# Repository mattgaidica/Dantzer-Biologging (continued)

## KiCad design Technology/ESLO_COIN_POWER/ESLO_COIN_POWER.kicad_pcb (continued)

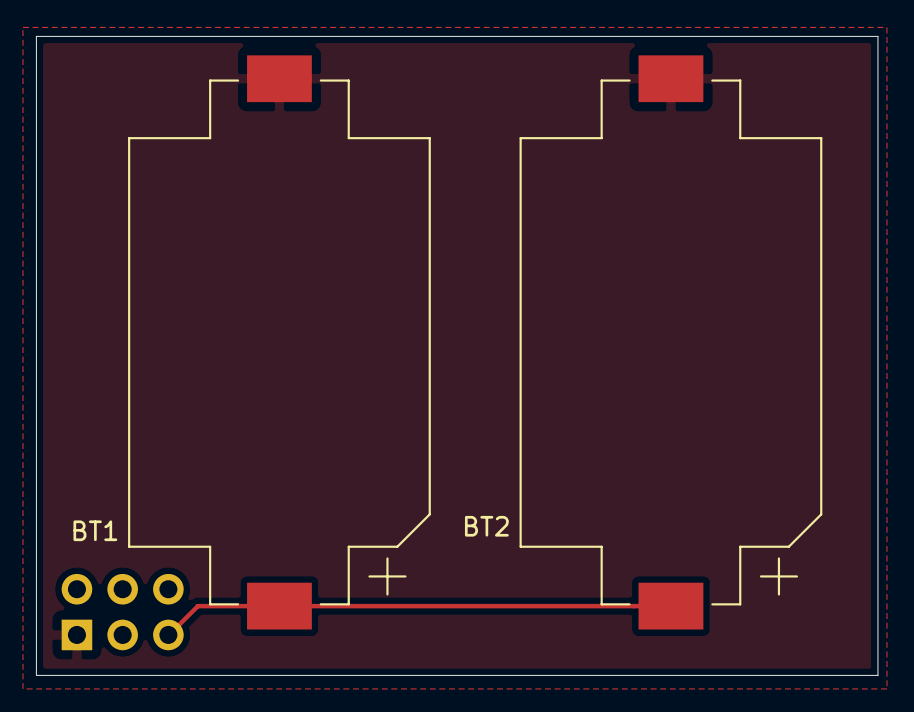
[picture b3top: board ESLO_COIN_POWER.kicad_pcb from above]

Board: 2 copper layers, 46.8 x 35.5 mm, 3 parts (1 on the bottom side), 2 nets.

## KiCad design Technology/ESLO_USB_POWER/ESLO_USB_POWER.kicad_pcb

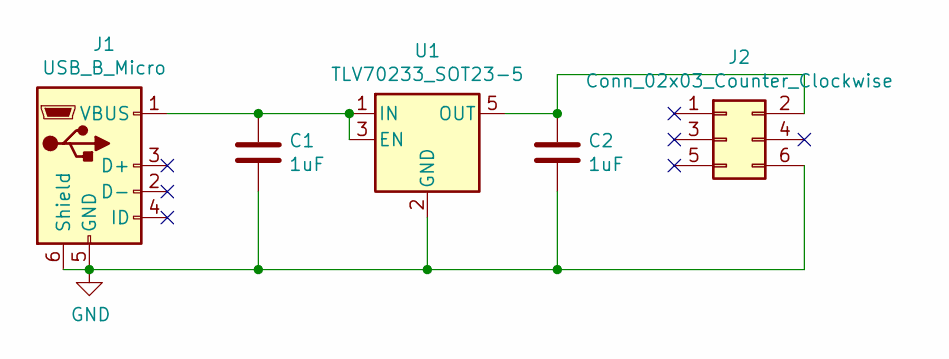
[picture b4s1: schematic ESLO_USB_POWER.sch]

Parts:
C1, C2: 1uF; C_0603_1608Metric; Digikey 399-11133-2-ND
J1: USB_B_Micro; USB_Micro-B_Molex-105017-0001; Digikey WM11262TR-ND
J2: Conn_02x03_Counter_Clockwise; PinSocket_2x03_P2.54mm_Vertical; Digikey A106656-ND
U1: TLV70233_SOT23-5; SOT-23-5; Digikey 296-39284-2-ND

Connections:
GND: C1.2, C2.2, J1.5 (GND), J1.6 (Shield), J2.6, U1.2 (GND)
unnamed: C1.1, J1.1 (VBUS), U1.1 (IN), U1.3 (EN)
unnamed: C2.1, J2.2, U1.5 (OUT)

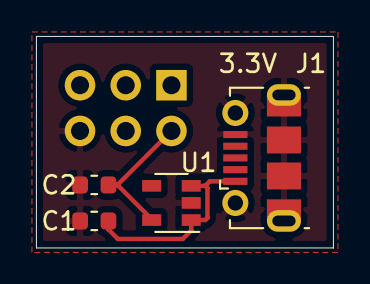
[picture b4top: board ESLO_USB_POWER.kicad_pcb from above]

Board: 2 copper layers, 16.5 x 11.8 mm, 5 parts (1 on the bottom side), 3 nets.

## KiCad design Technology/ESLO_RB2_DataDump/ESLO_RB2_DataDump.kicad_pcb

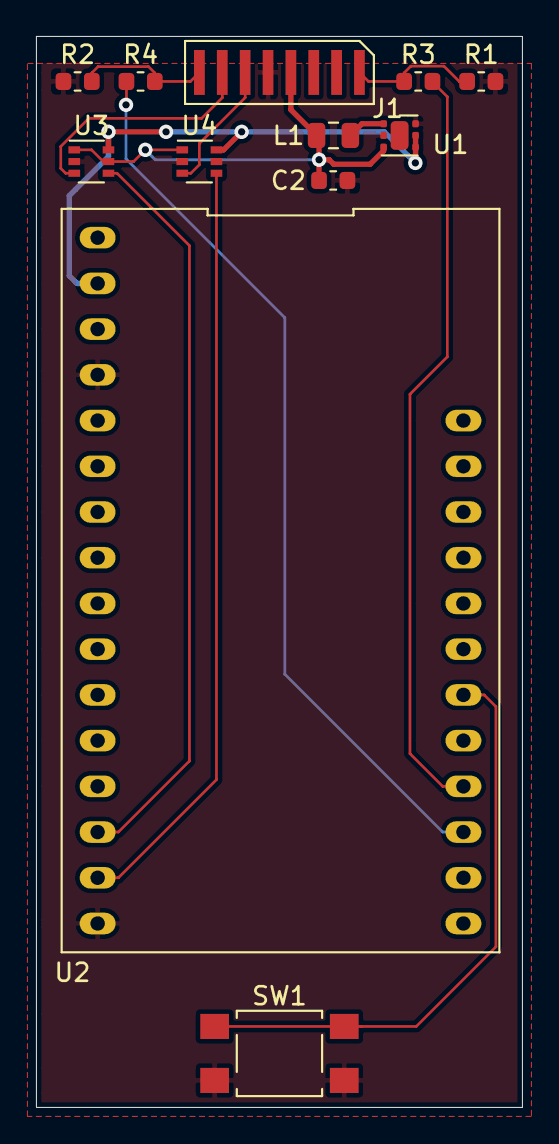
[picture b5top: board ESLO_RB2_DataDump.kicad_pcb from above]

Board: 2 copper layers, 27.0 x 59.5 mm, 12 parts (0 on the bottom side), 13 nets.

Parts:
C2: 10uF; C_0603_1608Metric
J1: Conn_01x08_Female; 8pin_1-27pitch_SMD
L1: 2.2uH; L_0805_2012Metric
R1, R2: 10k; R_0603_1608Metric
R3, R4: 8.25k; R_0603_1608Metric
SW1: SW_DPST; SW_SPST_TL3305A
U1: TPS62243_WSON; WSON-6-1EP_2x2mm_P0.65mm_EP1x1.6mm
U2: Adalogger; Adafruit_feather
U3, U4: SN74ACX1T45; SOT-363_SC-70-6

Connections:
+1V8: C2.1, J1.4, L1.2, U1.3, U3.1, U3.5, U4.1
+3V3: U1.4, U1.5, U2.2, U3.6, U4.6
DEBUG: R4.1, U2.19
GND: C2.2, J1.5, R1.1, R2.1, SW1.2, U1.2, U1.6, U2.4, U2.16, U3.2, U4.2, U4.5
unnamed: J1.1, R1.2, R3.2
unnamed: J1.8, R2.2, R4.2
unnamed: L1.1, U1.1
unnamed: SW1.1, U2.22
RESET: R3.1, U2.20
RX: U2.14, U3.4
RXD: J1.6, U4.3
TX: U2.15, U4.4
TXD: J1.7, U3.3

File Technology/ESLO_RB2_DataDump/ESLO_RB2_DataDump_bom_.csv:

Component,Description,Part,References,Value,Footprint,Quantity Per PCB,Datasheet,Digikey
1,Unpolarized capacitor,C,C2,10uF,C_0603_1608Metric,1,~,478-8050-1-ND
2,"Generic connector, single row, 01x08, script generated (kicad-library-utils/schlib/autogen/connector/)",Conn_01x08_Female,J1,Conn_01x08_Female,8pin_1-27pitch_SMD,1,~,ED90570-ND
3,Capacitor symbol for simulation only,INDUCTOR,L1,2.2uH,L_0805_2012Metric,1,~,490-4994-1-ND
4,Resistor,R,R1 R2,10k,R_0603_1608Metric,2,~,CR0603-JW-103ELFCT-ND
5,Resistor,R,R3 R4,8.25k,R_0603_1608Metric,2,~,RMCF0603FT8K25CT-ND
6,Double Pole Single Throw (DPST) Switch,SW_DPST,SW1,SW_DPST,SW_SPST_TL3305A,1,~,EG5353CT-ND
7,,Adalogger,U2,Adalogger,Adafruit_feather,1,,1528-1539-ND
8,,SN74ACX1T45,U3 U4,SN74ACX1T45,SOT-363_SC-70-6,2,,296-SN74AXC1T45QDCKRQ1CT-ND
9,,TPS62243_WSON,U1,TPS62243_WSON,WSON-6-1EP_2x2mm_P0.65mm_EP1x1.6mm,1,,TPS62243DRVR





Component Groups:,9
Component Count:,12
Fitted Components:,12
Number of PCBs:,1
Total components:,12
Schematic Version:,
Schematic Date:,
BoM Date:,"Wednesday, June 02, 2021 at 09:34:16 AM"
Schematic Source:,/Users/matt/Box Sync/Biologging/Technology/ESLO_RB2_DataDump/ESLO_RB2_DataDump.sch
KiCad Version:,Eeschema (5.1.5-0-10_14)

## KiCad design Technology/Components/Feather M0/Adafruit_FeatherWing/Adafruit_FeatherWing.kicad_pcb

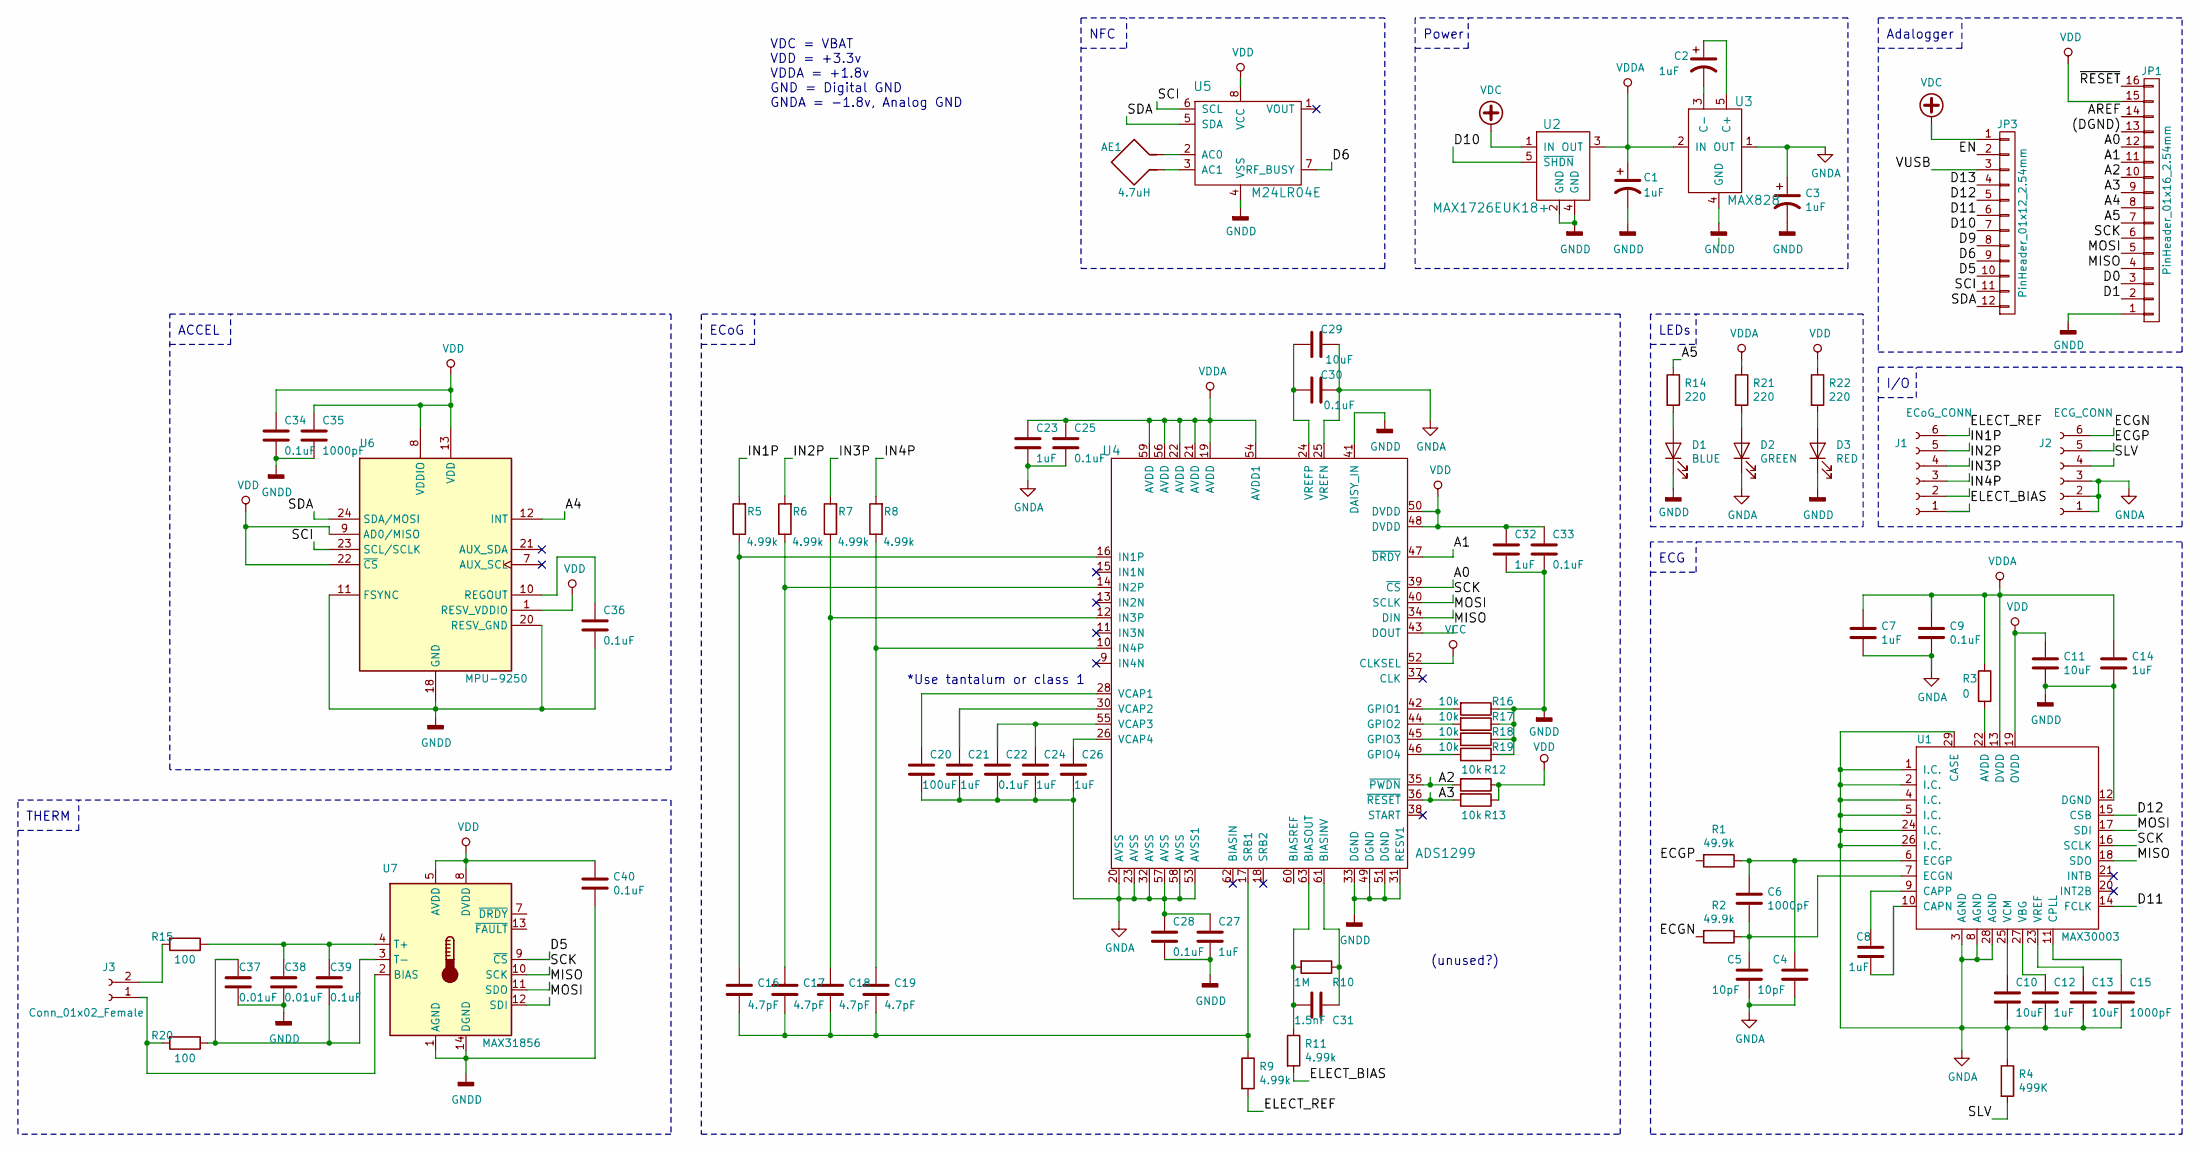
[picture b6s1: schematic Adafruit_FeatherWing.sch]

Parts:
AE1: 4.7uH; PA6512-AED
C1, C2, C3, C7, C8, C12, C14, C21, C23, C24, C26, C27, C32: 1uF; C_0603_1608Metric; Digikey# 1276-1102-1-ND
C4, C5: 10pF; C_0603_1608Metric; Digikey# 399-7815-1-ND
C6, C15, C35: 1000pF; C_0603_1608Metric; Digikey# 1276-1091-1-ND
C9, C22, C25, C28, C30, C33, C34, C36, C39, C40: 0.1uF; C_0603_1608Metric; Digikey# 399-1095-1-ND
C10, C11, C13: 10uF; C_0603_1608Metric; Digikey# 490-14372-1-ND
C16, C17, C18, C19: 4.7pF; C_0603_1608Metric; Digikey# 1276-1098-1-ND
C20: 100uF; C_1210_3225Metric; Digikey# 587-1388-1-ND
C29: 10uF; C_0805_2012Metric; Digikey# 1276-6456-1-ND
C31: 1.5nF; C_0805_2012Metric; Digikey# 399-16647-1-ND
C37, C38: 0.01uF; C_0603_1608Metric; Digikey# 399-17960-1-ND
D1: BLUE; LED_0603_1608Metric; Digikey# 160-1827-1-ND
D2: GREEN; LED_0603_1608Metric; Digikey# 160-1446-1-ND
D3: RED; LED_0603_1608Metric; Digikey# 160-1436-1-ND
J1: ECoG_CONN; ARBO_IO6
J2: ECG_CONN; ARBO_IO6
J3: Conn_01x02_Female; ARBO_THERM2
JP1: PinHeader_01x16_2.54mm; Conn_PinHeader_1x16; Digikey# 952-3304-ND
JP3: PinHeader_01x12_2.54mm; Conn_PinHeader_1x12; Digikey# 952-3302-ND
R1, R2: 49.9k; R_0603_1608Metric; Digikey# 311-49.9KHRCT-ND
R3: 0; R_0603_1608Metric; Digikey# 1276-3510-1-ND
R4: 499K; R_0603_1608Metric; Digikey# 541-3001-1-ND
R5, R6, R7, R8, R9, R11: 4.99k; R_0603_1608Metric; Digikey# 311-4.99KHRCT-ND
R10: 1M; R_0603_1608Metric; Digikey# 311-1.00MHRCT-ND
R12, R13, R16, R17, R18, R19: 10k; R_0603_1608Metric; Digikey# RNCP0603FTD10K0CT-ND
R14, R21, R22: 220; R_0603_1608Metric; Digikey# A130087CT-ND
R15, R20: 100; R_0603_1608Metric; Digikey# A102200CT-ND
U1: MAX30003; QFN-28-1EP_5x5mm_P0.5mm_EP3.35x3.35mm; Digikey# MAX30003CTI+TCT-ND
U2: MAX1726EUK18+; SOT-23-5; Digikey# MAX1726EUK18+T-ND
U3: MAX828; SOT-23-5; Digikey# MAX828EUK+TCT-ND
U4: ADS1299; TQFP-64_10x10mm_P0.5mm; Digikey# 296-45228-1-ND
U5: M24LR04E; TSSOP-8_4.4x3mm_P0.65mm; Digikey# 497-12878-1-ND
U6: MPU-9250; InvenSense_QFN-24_3x3mm_P0.4mm; Digikey# 1428-1019-1-ND
U7: MAX31856; TSSOP-14_4.4x5mm_P0.65mm; Digikey# MAX31856MUD+-ND

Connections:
/(DGND): JP1.13
/A0: JP1.12, U4.39 (~CS)
/A1: JP1.11, U4.47 (~DRDY)
/A2: JP1.10, R12.2, U4.35 (~PWDN)
/A3: JP1.9, R13.2, U4.36 (~RESET)
/A4: JP1.8, U6.12 (INT)
/A5: JP1.7, R14.1
/AREF: JP1.14
/D0: JP1.3
/D1: JP1.2
/D5: JP3.10, U7.9 (~CS)
/D6: JP3.9, U5.7 (RF_BUSY)
/D9: JP3.8
/D10: JP3.7, U2.5 (~SHDN)
/D11: JP3.6, U1.14 (FCLK)
/D12: JP3.5, U1.15 (CSB)
/D13: JP3.4
/ECGN: J2.6, R2.2
/ECGP: J2.5, R1.2
/ELECT_BIAS: J1.1, R11.2
/ELECT_REF: J1.6, R9.2
/EN: JP3.2
/IN1P: J1.5, R5.2
/IN2P: J1.4, R6.2
/IN3P: J1.3, R7.2
/IN4P: J1.2, R8.2
/MISO: JP1.4, U1.18 (SDO), U4.43 (DOUT), U7.11 (SDO)
/MOSI: JP1.5, U1.17 (SDI), U4.34 (DIN), U7.12 (SDI)
/SCI: JP3.11, U5.6 (SCL), U6.23 (SCL/SCLK)
/SCK: JP1.6, U1.16 (SCLK), U4.40 (SCLK), U7.10 (SCK)
/SDA: JP3.12, U5.5 (SDA), U6.24 (SDA/MOSI)
/SLV: J2.4, R4.2
/VUSB: JP3.3
/~RESET: JP1.16
GNDA: C3.1, C4.2, C5.2, C7.2, C9.2, C10.2, C12.2, C13.2, C15.2, C20.2, C21.2, C22.2, C23.2, C24.2, C25.2, C26.2, C27.1, C28.1, C29.1, C30.1, D2.1 (K), J2.1, J2.2, J2.3, R4.1, U1.1 (I.C.), U1.2 (I.C.), U1.3 (AGND), U1.4 (I.C.), U1.5 (I.C.), U1.8 (AGND), U1.24 (I.C.), U1.26 (I.C.), U1.28 (AGND), U1.29 (CASE), U3.1 (OUT), U4.20 (AVSS), U4.23 (AVSS), U4.25 (VREFN), U4.32 (AVSS), U4.53 (AVSS1), U4.57 (AVSS), U4.58 (AVSS)
GNDD: C1.2, C3.2, C11.2, C14.2, C27.2, C28.2, C32.2, C33.2, C34.2, C35.2, C36.2, C37.2, C38.2, C40.2, D1.1 (K), D3.1 (K), JP1.1, R16.1, R17.1, R18.1, R19.1, U1.12 (DGND), U2.2 (GND), U2.4 (GND), U3.4 (GND), U4.31 (RESV1), U4.33 (DGND), U4.41 (DAISY_IN), U4.49 (DGND), U4.51 (DGND), U5.4 (VSS), U6.11 (FSYNC), U6.18 (GND), U6.20 (RESV_GND), U7.1 (AGND), U7.14 (DGND)
unnamed: AE1.1, U5.3 (AC1)
unnamed: AE1.2, U5.2 (AC0)
unnamed: C2.1, U3.5 (C+)
unnamed: C2.2, U3.3 (C-)
unnamed: C4.1, C6.1, R1.1, U1.6 (ECGP)
unnamed: C5.1, C6.2, R2.1, U1.7 (ECGN)
unnamed: C8.1, U1.9 (CAPP)
unnamed: C8.2, U1.10 (CAPN)
unnamed: C10.1, U1.25 (VCM)
unnamed: C12.1, U1.27 (VBG)
unnamed: C13.1, U1.23 (VREF)
unnamed: C15.1, U1.11 (CPLL)
unnamed: C16.1, R5.1, U4.16 (IN1P)
unnamed: C16.2, C17.2, C18.2, C19.2, R9.1, U4.17 (SRB1)
unnamed: C17.1, R6.1, U4.14 (IN2P)
unnamed: C18.1, R7.1, U4.12 (IN3P)
unnamed: C19.1, R8.1, U4.10 (IN4P)
unnamed: C20.1, U4.28 (VCAP1)
unnamed: C21.1, U4.30 (VCAP2)
unnamed: C22.1, C24.1, U4.55 (VCAP3)
unnamed: C26.1, U4.26 (VCAP4)
unnamed: C29.2, C30.2, U4.24 (VREFP)
unnamed: C31.1, R10.1, U4.61 (BIASINV)
unnamed: C31.2, R10.2, R11.1, U4.63 (BIASOUT)
unnamed: C36.1, U6.10 (REGOUT)
unnamed: C37.1, C39.2, R20.1, U7.3 (T-)
unnamed: C38.1, C39.1, R15.1, U7.4 (T+)
unnamed: D1.2 (A), R14.2
unnamed: D2.2 (A), R21.2
unnamed: D3.2 (A), R22.2
unnamed: J3.1, R20.2, U7.2 (BIAS)
unnamed: J3.2, R15.2
unnamed: R3.2, U1.22 (AVDD)
unnamed: R16.2, U4.42 (GPIO1)
unnamed: R17.2, U4.44 (GPIO2)
unnamed: R18.2, U4.45 (GPIO3)
unnamed: R19.2, U4.46 (GPIO4)
VCC: U4.52 (CLKSEL)
VDC: JP3.1, U2.1 (IN)
VDD: C11.1, C32.1, C33.1, C34.1, C35.1, C40.1, JP1.15, R12.1, R13.1, R22.1, U1.19 (OVDD), U4.48 (DVDD), U4.50 (DVDD), U5.8 (VCC), U6.1 (RESV_VDDIO), U6.8 (VDDIO), U6.9 (AD0/MISO), U6.13 (VDD), U6.22 (~CS), U7.5 (AVDD), U7.8 (DVDD)
VDDA: C1.1, C7.1, C9.1, C14.1, C23.1, C25.1, R3.1, R21.1, U1.13 (DVDD), U2.3 (OUT), U3.2 (IN), U4.19 (AVDD), U4.21 (AVDD), U4.22 (AVDD), U4.54 (AVDD1), U4.56 (AVDD), U4.59 (AVDD)

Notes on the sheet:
Adalogger
ECG
Power
*Use tantalum or class 1
VDC = VBAT VDD = +3.3v VDDA = +1.8v GND = Digital GND GNDA = -1.8v, Analog GND
(unused?)
ECoG
NFC
LEDs
I/O
ACCEL
THERM

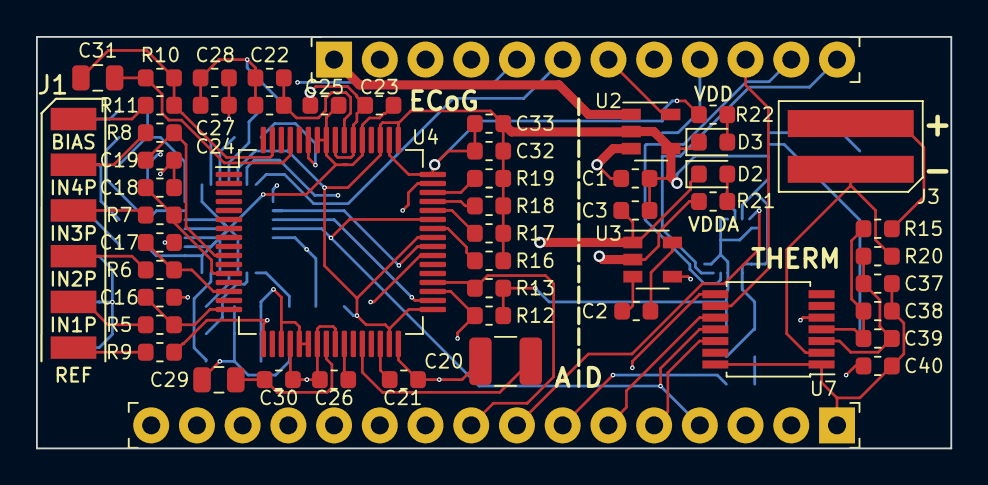
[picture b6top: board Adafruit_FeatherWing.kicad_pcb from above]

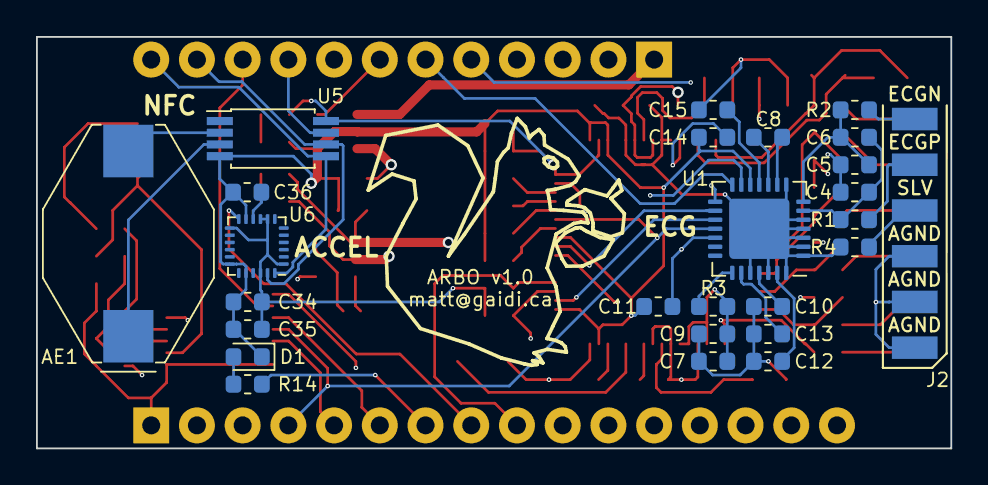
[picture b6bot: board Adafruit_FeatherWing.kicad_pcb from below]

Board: 4 copper layers, 50.8 x 22.9 mm, 78 parts (26 on the bottom side), 67 nets.

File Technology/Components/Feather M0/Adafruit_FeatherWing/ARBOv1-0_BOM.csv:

Component,Description,Part,References,Value,Footprint,Quantity Per PCB,Datasheet,Manf#,Digikey#,Optn,Manf
1,Loop antenna,Antenna_Loop,AE1,4.7uH,PA6512-AED,1,~,,,,
2,Unpolarized capacitor,C,C37 C38,0.01uF,C_0603_1608Metric,2,~,C0603C103KARACAUTO,399-17960-1-ND,,
3,Unpolarized capacitor,C,C9 C22 C25 C28 C30 C33 C34 C36 C39 C40,0.1uF,C_0603_1608Metric,10,~,C0603C104K8RACTU,399-1095-1-ND,,
4,Unpolarized capacitor,C,C31,1.5nF,C_0805_2012Metric,1,~,C0805C152KDRACAUTO,399-16647-1-ND,,
5,Unpolarized capacitor,C,C6 C15 C35,1000pF,C_0603_1608Metric,3,~,CL10C102JB8NNNC,1276-1091-1-ND,,
6,Unpolarized capacitor,C,C20,100uF,C_1210_3225Metric,1,~,JMK325BJ107MY-T,587-1388-1-ND,,
7,Unpolarized capacitor,C,C4 C5,10pF,C_0603_1608Metric,2,~,C0603C100D5GACTU,399-7815-1-ND,,
8,Unpolarized capacitor,C,C10 C11 C13,10uF,C_0603_1608Metric,3,~,GRM188R61A106KE69J,490-14372-1-ND,,
9,Unpolarized capacitor,C,C29,10uF,C_0805_2012Metric,1,~,CL21A106KPFNNNG,1276-6456-1-ND,,
10,"Polarized capacitor, US symbol",CP1,C1 C2 C3,1uF,C_0603_1608Metric,3,~,CL10A105KA8NNNC,1276-1102-1-ND,,
11,Unpolarized capacitor,C,C7 C8 C12 C14 C21 C23 C24 C26 C27 C32,1uF,C_0603_1608Metric,10,~,CL10A105KA8NNNC,1276-1102-1-ND,,
12,Unpolarized capacitor,C,C16 C17 C18 C19,4.7pF,C_0603_1608Metric,4,~,CL10B472KB8NNNC,1276-1098-1-ND,,
13,Light emitting diode,LED,D1,BLUE,LED_0603_1608Metric,1,~,LTST-C193TBKT-5A,160-1827-1-ND,,
14,Light emitting diode,LED,D2,GREEN,LED_0603_1608Metric,1,~,LTST-C191KGKT,160-1446-1-ND,,
15,Light emitting diode,LED,D3,RED,LED_0603_1608Metric,1,~,LTST-C190KRKT,160-1436-1-ND,,
16,"Generic connector, single row, 01x02, script generated (kicad-library-utils/schlib/autogen/connector/)",Conn_01x02_Female,J3,Conn_01x02_Female,ARBO_THERM2,1,~,,,,
17,"Generic connector, single row, 01x06, script generated (kicad-library-utils/schlib/autogen/connector/)",Conn_01x06_Female,J1 J2,ECoG_CONN,ARBO_IO6,2,~,,,,
18,,CONN_01X12,JP3,PinHeader_01x12_2.54mm,Conn_PinHeader_1x12,1,,M20-9991245,952-3302-ND,,
19,,CONN_01X16,JP1,PinHeader_01x16_2.54mm,Conn_PinHeader_1x16,1,,M20-9991645,952-3304-ND,_,_
20,Resistor,R,R3,0,R_0603_1608Metric,1,~,RC1608J000CS,1276-3510-1-ND,,
21,Resistor,R,R15 R20,100,R_0603_1608Metric,2,~,CPF0603F100RC1,A102200CT-ND,,
22,Resistor,R,R12 R13 R16 R17 R18 R19,10k,R_0603_1608Metric,6,~,RNCP0603FTD10K0,RNCP0603FTD10K0CT-ND,,
23,Resistor,R,R10,1M,R_0603_1608Metric,1,~,RC0603FR-071ML,311-1.00MHRCT-ND,,
24,Resistor,R,R14 R21 R22,220,R_0603_1608Metric,3,~,CRGCQ0603J220R,A130087CT-ND,,
25,Resistor,R,R5 R6 R7 R8 R9 R11,4.99k,R_0603_1608Metric,6,~,RC0603FR-074K99L,311-4.99KHRCT-ND,,
26,Resistor,R,R1 R2,49.9k,R_0603_1608Metric,2,~,RC0603FR-0749K9L,311-49.9KHRCT-ND,,
27,Resistor,R,R4,499K,R_0603_1608Metric,1,~,CRCW0603499KFKTA,541-3001-1-ND,,
28,,ADS1299,U4,ADS1299,TQFP-64_10x10mm_P0.5mm,1,,ADS1299-4PAGR,296-45228-1-ND,,
29,,M24LR04E,U5,M24LR04E,TSSOP-8_4.4x3mm_P0.65mm,1,,M24LR04E-RMN6T/2,497-12878-1-ND,,
30,,MAX1726EUK18+,U2,MAX1726EUK18+,SOT-23-5,1,,MAX1726EUK18+T,MAX1726EUK18+T-ND,,
31,,MAX30003,U1,MAX30003,QFN-28-1EP_5x5mm_P0.5mm_EP3.35x3.35mm,1,,MAX30003CTI+T,MAX30003CTI+TCT-ND,,
32,"Precision Thermocouple to Digital Converter with Linearization, TSSOP-14",MAX31856,U7,MAX31856,TSSOP-14_4.4x5mm_P0.65mm,1,https://datasheets.maximintegrated.com/en/ds/MAX31856.pdf,MAX31856MUD+,MAX31856MUD+-ND,,
33,,MAX828,U3,MAX828,SOT-23-5,1,,MAX828EUK+T,MAX828EUK+TCT-ND,,
34,"InvenSense 9-Axis Motion Sensor, Accelerometer, Gyroscope, Compass, I2C/SPI",MPU-9250,U6,MPU-9250,InvenSense_QFN-24_3x3mm_P0.4mm,1,https://store.invensense.com/datasheets/invensense/MPU9250RE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,MPU-9250,1428-1019-1-ND,,





Component Groups:,34
Component Count:,78
Fitted Components:,78
Number of PCBs:,1
Total components:,78
Schematic Version:,
Schematic Date:,sam. 04 avril 2015
BoM Date:,"Monday, June 03, 2019 at 06:41:01 PM"
Schematic Source:,/Users/mattgaidica/Dropbox/Projects/ARBO/PCB/Arduino M0/Adafruit_FeatherWing/Adafruit_FeatherWing.sch
KiCad Version:,Eeschema (5.1.2-1)-1

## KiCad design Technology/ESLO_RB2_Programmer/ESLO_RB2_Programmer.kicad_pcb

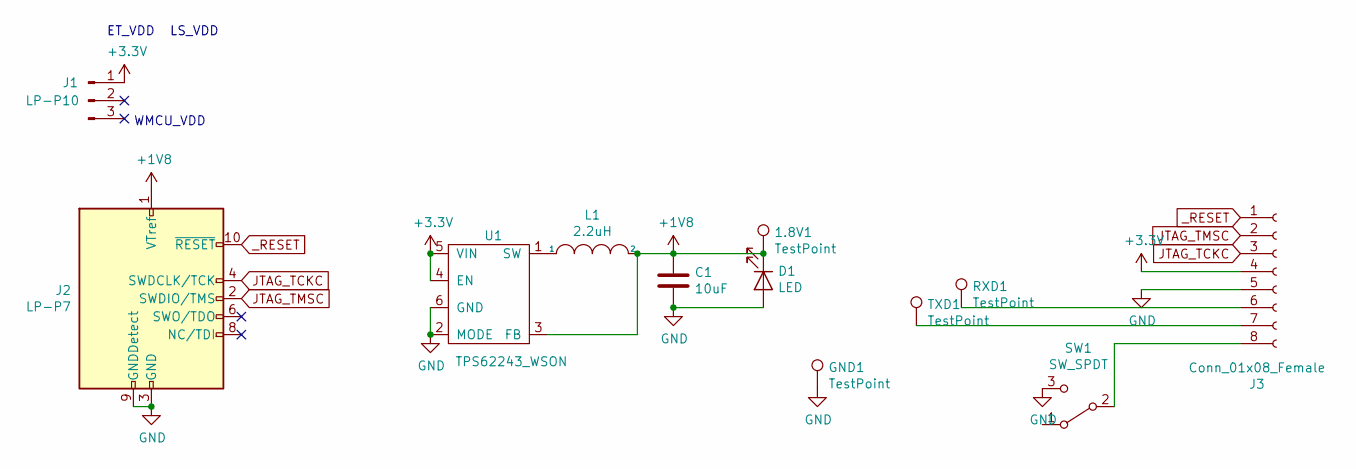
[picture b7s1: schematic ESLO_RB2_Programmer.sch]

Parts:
1.8V1: TestPoint; TestPoint_Keystone_5010-5014_Multipurpose; Digikey 36-5014-ND
C1: 10uF; C_0603_1608Metric; Digikey 478-8050-1-ND‎
D1: LED; D_0603_1608Metric; Digikey 475-3442-1-ND
GND1: TestPoint; TestPoint_Keystone_5010-5014_Multipurpose; Digikey 36-5014-ND
J1: LP-P10; PinHeader_1x03_P2.54mm_Vertical; Digikey A19430-ND
J2: LP-P7; PinHeader_2x05_P1.27mm_Vertical_SMD; Digikey SAM13165CT-ND
J3: Conn_01x08_Female; 8pin_1-27pitch_SMD; Digikey ED90570-ND
L1: 2.2uH; R_0805_2012Metric; Digikey 490-4994-1-ND‎
RXD1: TestPoint; TestPoint_Keystone_5010-5014_Multipurpose; Digikey 36-5014-ND
SW1: SW_SPDT; PinSocket_1x03_P2.54mm_Vertical; Digikey 360-2133-ND
TXD1: TestPoint; TestPoint_Keystone_5010-5014_Multipurpose; Digikey 36-5014-ND
U1: TPS62243_WSON; WSON-6-1EP_2x2mm_P0.65mm_EP1x1.6mm; Digikey 296-46476-1-ND‎

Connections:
+1V8: 1.8V1.1, C1.1, D1.1 (K), J2.1 (VTref), L1.2, U1.3 (FB)
+3V3: J1.1, J3.4, U1.4 (EN), U1.5 (VIN)
GND: C1.2, D1.2 (A), GND1.1, J2.3 (GND), J2.5 (GND), J2.9 (GNDDetect), J3.5, SW1.3 (C), U1.2 (MODE), U1.6 (GND)
JTAG_TCKC: J2.4 (SWDCLK/TCK), J3.3
JTAG_TMSC: J2.2 (SWDIO/TMS), J3.2
unnamed: J3.6, RXD1.1
unnamed: J3.7, TXD1.1
unnamed: J3.8, SW1.2 (B)
unnamed: L1.1, U1.1 (SW)
_RESET: J2.10 (~RESET~), J3.1

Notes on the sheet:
ET_VDD
LS_VDD
WMCU_VDD

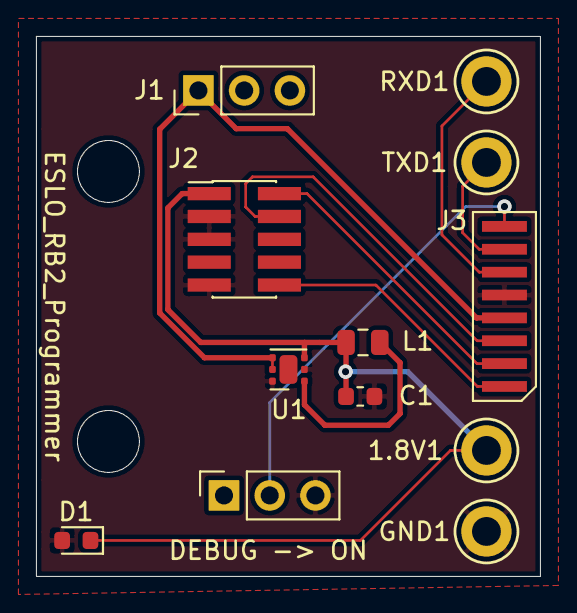
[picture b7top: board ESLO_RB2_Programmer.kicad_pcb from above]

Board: 2 copper layers, 28.0 x 30.0 mm, 12 parts (0 on the bottom side), 10 nets.

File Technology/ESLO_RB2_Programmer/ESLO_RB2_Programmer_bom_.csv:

Component,Description,Part,References,Value,Footprint,Quantity Per PCB,Datasheet,Digikey
1,Unpolarized capacitor,C,C1,10uF,C_0603_1608Metric,1,~,478-8050-1-ND‎
2,Light emitting diode,LED,D1,LED,D_0603_1608Metric,1,~,475-3442-1-ND
3,"Generic connector, single row, 01x08, script generated (kicad-library-utils/schlib/autogen/connector/)",Conn_01x08_Female,J3,Conn_01x08_Female,8pin_1-27pitch_SMD,1,~,ED90570-ND
4,"Generic connector, single row, 01x03, script generated (kicad-library-utils/schlib/autogen/connector/)",Conn_01x03_Male,J1,LP-P10,PinHeader_1x03_P2.54mm_Vertical,1,conn-SAM8930-ND,A19430-ND
5,"Cortex Debug Connector, standard ARM Cortex-M SWD and JTAG interface",Conn_ARM_JTAG_SWD_10,J2,LP-P7,PinHeader_2x05_P1.27mm_Vertical_SMD,1,http://infocenter.arm.com/help/topic/com.arm.doc.ddi0314h/DD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,SAM13165CT-ND
6,Capacitor symbol for simulation only,INDUCTOR,L1,2.2uH,R_0805_2012Metric,1,~,490-4994-1-ND‎
7,"Switch, single pole double throw",SW_SPDT,SW1,SW_SPDT,PinSocket_1x03_P2.54mm_Vertical,1,~,360-2133-ND
8,,TPS62243_WSON,U1,TPS62243_WSON,WSON-6-1EP_2x2mm_P0.65mm_EP1x1.6mm,1,,296-46476-1-ND‎





Component Groups:,8
Component Count:,8
Fitted Components:,8
Number of PCBs:,1
Total components:,8
Schematic Version:,
Schematic Date:,
BoM Date:,"Wednesday, June 02, 2021 at 09:28:16 AM"
Schematic Source:,/Users/matt/Box Sync/Biologging/Technology/ESLO_RB2_Programmer/ESLO_RB2_Programmer.sch
KiCad Version:,Eeschema (5.1.5-0-10_14)

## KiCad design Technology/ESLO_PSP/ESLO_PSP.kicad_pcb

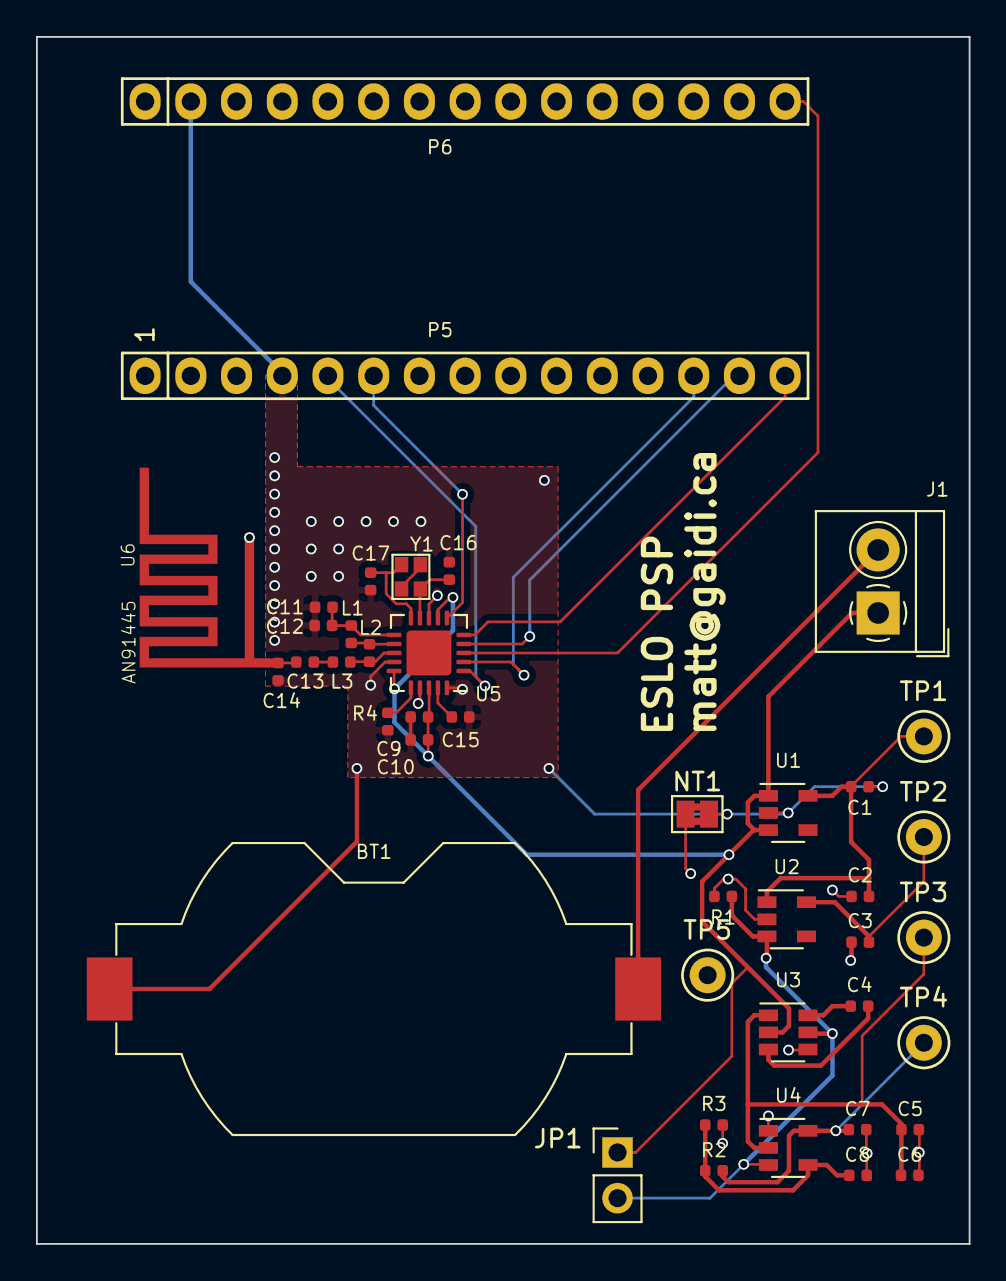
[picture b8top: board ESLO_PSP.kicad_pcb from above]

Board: 2 copper layers, 51.8 x 67.1 mm, 42 parts (0 on the bottom side), 27 nets.

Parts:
BT1: Coin Cell; BatteryHolder_Keystone_1058_1x2032
C1, C2, C3: 1uF; C_0402_1005Metric
C4, C5: 10uF; C_0402_1005Metric
C6, C7: 2.2uF; C_0402_1005Metric
C8, C9: 10nF; C_0402_1005Metric
C10: 1nF; C_0402_1005Metric
C11: 4.7pF; C_0402_1005Metric
C12: 2.2nF; C_0402_1005Metric
C13: 1.5pF; C_0402_1005Metric
C14: 1pF; C_0402_1005Metric
C15: 33nF; C_0402_1005Metric
C16, C17: 22pF; C_0402_1005Metric
J1: Imeas; TerminalBlock_4Ucon_1x02_P3.50mm_Horizontal
JP1: Jumper; PinHeader_1x02_P2.54mm_Vertical
L1: 2.7nH; L_0402_1005Metric
L2: 8.2nH; L_0402_1005Metric
L3: 3.9nH; L_0402_1005Metric
NT1: Net-Tie_2; SolderJumper-2_P1.3mm_Bridged2Bar_Pad1.0x1.5mm
P5: Digital; Socket_Strip_Arduino_1x15
P6: Analog; Socket_Strip_Arduino_1x15
R1: 10k; R_0402_1005Metric
R2: 33k; R_0402_1005Metric
R3: 63.4k; R_0402_1005Metric
R4: 22k; R_0402_1005Metric
TP1: TP1.8; TestPoint_Keystone_5000-5004_Miniature
TP2: TP1.5; TestPoint_Keystone_5000-5004_Miniature
TP3: TP-3; TestPoint_Keystone_5000-5004_Miniature
TP4: TP-1.5; TestPoint_Keystone_5000-5004_Miniature
TP5: TPGNDD; TestPoint_Keystone_5000-5004_Miniature
U1: LP5907MFX-1.8; SOT-23-5
U2: LP5907MFX-1.5; SOT-23-5
U3: MAX1720; SOT-23-6
U4: TPS72301DDCT; SOT-23-5
U5: nRF24L01P; QFN-20-1EP_4x4mm_P0.5mm_EP2.5x2.5mm
U6: AN91445; AN91445_MG
Y1: SXT21412AA16; SXT214

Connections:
+1V8: C1.2, C2.2, TP1.1, U1.5, U2.1
+BATT: C9.1, C10.1, J1.1, JP1.1, U1.1, U1.3, U3.2, U5.7, U5.15, U5.18
CE: P5.5, U5.1
GNDA: C2.1, C3.1, C5.1, C6.1, C7.1, C8.1, NT1.1, R1.2, R3.2, TP5.1, U2.2, U3.4, U4.1
GNDD: BT1.2, C1.1, C9.2, C10.2, C11.2, C12.2, C14.2, C15.2, C16.2, C17.2, NT1.2, P5.4, P6.2, R4.2, U1.2, U5.8, U5.14, U5.17, U5.20, Y1.2, Y1.4
IRQ: P5.6, U5.6
MISO: P5.15, U5.5
MOSI: P5.14, U5.4
unnamed: BT1.1, J1.2
unnamed: C4.1, U3.6
unnamed: C4.2, U3.3
unnamed: C5.2, C6.2, TP3.1, U3.1, U4.2
unnamed: C8.2, R2.2, R3.1, U4.4
unnamed: C11.1, C12.1, L1.2, U5.11
unnamed: C13.1, L3.2
unnamed: C13.2, C14.1, U6.1
unnamed: C15.1, U5.19
unnamed: C16.1, U5.9, Y1.1
unnamed: C17.1, U5.10, Y1.3
unnamed: L1.1, L2.1, U5.12
unnamed: L2.2, L3.1, U5.13
unnamed: R4.1, U5.16
SCK: P6.15, U5.3
SS: P5.13, U5.2
VDDA: C3.2, TP2.1, U2.5
VSSA: C7.2, R2.1, TP4.1, U4.5
~SHDN: JP1.2, R1.1, U2.3, U3.5, U4.3

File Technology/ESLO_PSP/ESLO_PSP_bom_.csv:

Component,Description,Part,References,Value,Footprint,Quantity Per PCB,Datasheet,Digikey
1,Single-cell battery,Battery_Cell,BT1,Coin Cell,BatteryHolder_Keystone_1058_1x2032,1,~,36-1058-ND
2,Unpolarized capacitor,C,C13,1.5pF,C_0402_1005Metric,1,~,490-6212-2-ND
3,Unpolarized capacitor,C,C8 C9,10nF,C_0402_1005Metric,2,~,490-6326-2-ND
4,Unpolarized capacitor,C,C10,1nF,C_0402_1005Metric,1,~,490-6350-2-ND
5,Unpolarized capacitor,C,C14,1pF,C_0402_1005Metric,1,~,490-6206-2-ND
6,Unpolarized capacitor,C,C1 C2 C3 C4 C5,1uF,C_0402_1005Metric,5,~,399-4873-1-ND
7,Unpolarized capacitor,C,C12,2.2nF,C_0402_1005Metric,1,~,311-1037-1-ND
8,Unpolarized capacitor,C,C6 C7,2.2uF,C_0402_1005Metric,2,~,490-10451-1-ND
9,Unpolarized capacitor,C,C16 C17,22pF,C_0402_1005Metric,2,~,311-1652-1-ND
10,Unpolarized capacitor,C,C15,33nF,C_0402_1005Metric,1,~,490-11984-2-ND
11,Unpolarized capacitor,C,C11,4.7pF,C_0402_1005Metric,1,~,490-5874-2-ND
12,"Generic screw terminal, single row, 01x02, script generated (kicad-library-utils/schlib/autogen/connector/)",Screw_Terminal_01x02,J1,Imeas,TerminalBlock_4Ucon_1x02_P3.50mm_Horizontal,1,~,
13,"Jumper, normally closed",Jumper,JP1,Jumper,PinHeader_1x02_P2.54mm_Vertical,1,~,S9337-ND
14,Inductor,L,L1,2.7nH,L_0402_1005Metric,1,~,2035-0402HP-2N7EJTSCT-ND
15,Inductor,L,L3,3.9nH,L_0402_1005Metric,1,~,2035-0402HS-3N9EGTSCT-ND
16,Inductor,L,L2,8.2nH,L_0402_1005Metric,1,~,2035-1500-1-ND
17,"Net tie, 2 pins",Net-Tie_2,NT1,Net-Tie_2,SolderJumper-2_P1.3mm_Bridged2Bar_Pad1.0x1.5mm,1,~,
18,"Generic connector, single row, 01x15, script generated (kicad-library-utils/schlib/autogen/connector/)",Conn_01x15,P5 P6,Digital,Socket_Strip_Arduino_1x15,2,,S7013-ND
19,Resistor,R,R1,10k,R_0402_1005Metric,1,~,311-10.0KLRCT-ND
20,Resistor,R,R4,22k,R_0402_1005Metric,1,~,311-22.0KLRCT-ND
21,Resistor,R,R2,33k,R_0402_1005Metric,1,~,P33KDCCT-ND
22,Resistor,R,R3,63.4k,R_0402_1005Metric,1,~,YAG3204CT-ND
23,,AN91445_MG,U6,AN91445,AN91445_MG,1,,
24,"250-mA Ultra-Low-Noise Low-IQ LDO, 1.5V, SOT-23",LP5907MFX-1.5,U2,LP5907MFX-1.5,SOT-23-5,1,http://www.ti.com/lit/ds/symlink/lp5907.pdf,296-40355-1-ND
25,"250-mA Ultra-Low-Noise Low-IQ LDO, 1.8V, SOT-23",LP5907MFX-1.8,U1,LP5907MFX-1.8,SOT-23-5,1,http://www.ti.com/lit/ds/symlink/lp5907.pdf,296-41463-1-ND
26,,MAX1720,U3,MAX1720,SOT-23-6,1,,MAX1720EUTGOSCT-ND
27,,TPS72325,U4,TPS72301DDCT,SOT-23-5,1,,296-38438-1-ND
28,"nRF24L01+, Ultra low power 2.4GHz RF Transceiver, QFN20 4x4mm",nRF24L01P,U5,nRF24L01P,QFN-20-1EP_4x4mm_P0.5mm_EP2.5x2.5mm,1,http://www.nordicsemi.com/eng/content/download/2726/34069/fi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,1490-1033-1-ND
29,"Four pin crystal, GND on pins 2 and 4, small symbol",Crystal_GND24_Small,Y1,SXT21412AA16,SXT214,1,~,2388-SXT21412AA16-16.000M-ND





Component Groups:,29
Component Count:,37
Fitted Components:,37
Number of PCBs:,1
Total components:,37
Schematic Version:,
Schematic Date:,jeu. 02 avril 2015
BoM Date:,"Thursday, August 20, 2020 at 12:32:59 PM"
Schematic Source:,/Users/matt/Box Sync/Biologging/Technology/ESLO_PSP/ESLO_PSP.sch
KiCad Version:,Eeschema (5.1.5-0-10_14)

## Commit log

2019-12-05 Set theme jekyll-theme-minimal
2019-12-05 add gitignore
2019-12-05 Including Testbed design
2019-12-05 Including KiCad
2019-12-06 Create CNAME
2019-12-06 Update CNAME
2019-12-06 change theme
2019-12-06 update theme
2019-12-06 logo
2019-12-06 updating layout
2019-12-06 changed logo size
2019-12-06 added css for future
2019-12-06 updated logo
2019-12-06 homepage
2019-12-06 squirrels
2019-12-06 smaller
2019-12-06 adjust footer
2019-12-06 borders
2019-12-07 css ext
2019-12-07 adding testbed
2019-12-07 new logo
2019-12-09 squirrel platform
2019-12-10 show light dark
2019-12-14 Wiki QR code
2019-12-21 Updated testbed
2020-01-06 Updating values to match changes on board
2020-01-07 ARBO Mini hackathon
2020-01-08 Exported gerbers
2020-01-09 ARBO mini sent to JSTPCB for fab
2020-01-23 ARBO mini FRAM pads are backwards, fix later
2020-03-04 Changing RF design for BT
2020-04-01 Added ARBO BT and NUTS
2020-04-03 Got Nuts PCB prototype working, needs updates
2020-07-27 Working on pink noise
2020-08-12 Working on ESLO
2020-08-16 Making progress on ESLO
2020-08-18 Added ESLO
2020-08-21 ESLO changelog
2020-08-21 rm changelog
2020-08-25 Added ESLO debugger and PSP
2020-08-28 ESLO project updates
2020-09-02 Reconsidering ESLO architecture (-> CC2640R2)
2020-09-03 Datasheets
2020-09-03 allow all assets
2020-09-16 new RF footprints
2020-09-18 ESLO RB
2020-09-23 Redo ESLO_RB with AC coupling
2020-09-24 Completed RB design
2020-09-24 Checked all pins, ready for production
2020-09-28 Submit ESLO_RB for mfg w PCBONLINE
2020-10-04 Debugger submitted
2020-10-21 Assembling ESLO_RB
2020-10-27 ESLO Updates
2020-10-31 Debugging ESLO PBCs
2020-11-05 Debugging
2020-11-08 Cleaning
2020-11-10 Submitted ESLO_RB for TI hardware review
2020-11-17 Weblocs
2020-11-29 Added BTE docs
2020-12-01 Notes
2020-12-08 Added notes
2020-12-15 rm ds_store
2021-01-19 NAND updates
2021-02-17 Updated note on ESLO_RB
2021-02-20 kicad
2021-02-22 New thermistor datasheets
2021-02-23 Seeking LSM303AGR
2021-05-14 ESLO RB2
2021-05-26 ESLO Parts
2021-06-08 Adding all schematics/layouts/tech projects
2021-06-29 Schematics
2021-07-12 Comments
2021-07-28 Update schematics
